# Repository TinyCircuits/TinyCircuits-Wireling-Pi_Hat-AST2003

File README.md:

# TinyCircuits Wireling Pi Hat AST2003
# AST2003 Rev2

The design files are located under design_files/ for the TinyCircuits AST2003 Rev 2 PCB. This is a Pi Hat that allows Pi users to add up to 4 Wirelings to their project. 

Format is in Cadsoft Eagle format - Eagle version 6.2 was used for the original design.

For more infomation on this, check out the product page at TinyCircuits.com

# License:

Design by TinyCircuits.
All design files are released under the Creative Commons Attribution Share-Alike 3.0 License, see the following link for details: http://creativecommons.org/licenses/by-sa/3.0

All text above must be included in any redistribution or derived design

This project uses designs and concepts developed as part of the Arduino project and the LilyPad project.  The TinyCircuits design files themselves (schematics, PCB and libraries) are not directly derived from these works' design files and have been created new, however the concepts and basic architecture behind the TinyDuino and TinyLily products are derived and we thank the hard work of the organizations below for their contributions to open-source hardware:
  
Original Arduino Uno Design by Team Arduino

LilyPad Arduino Design by Leah Buechley and Sparkfun Electronics

Please support the open-source hardware community

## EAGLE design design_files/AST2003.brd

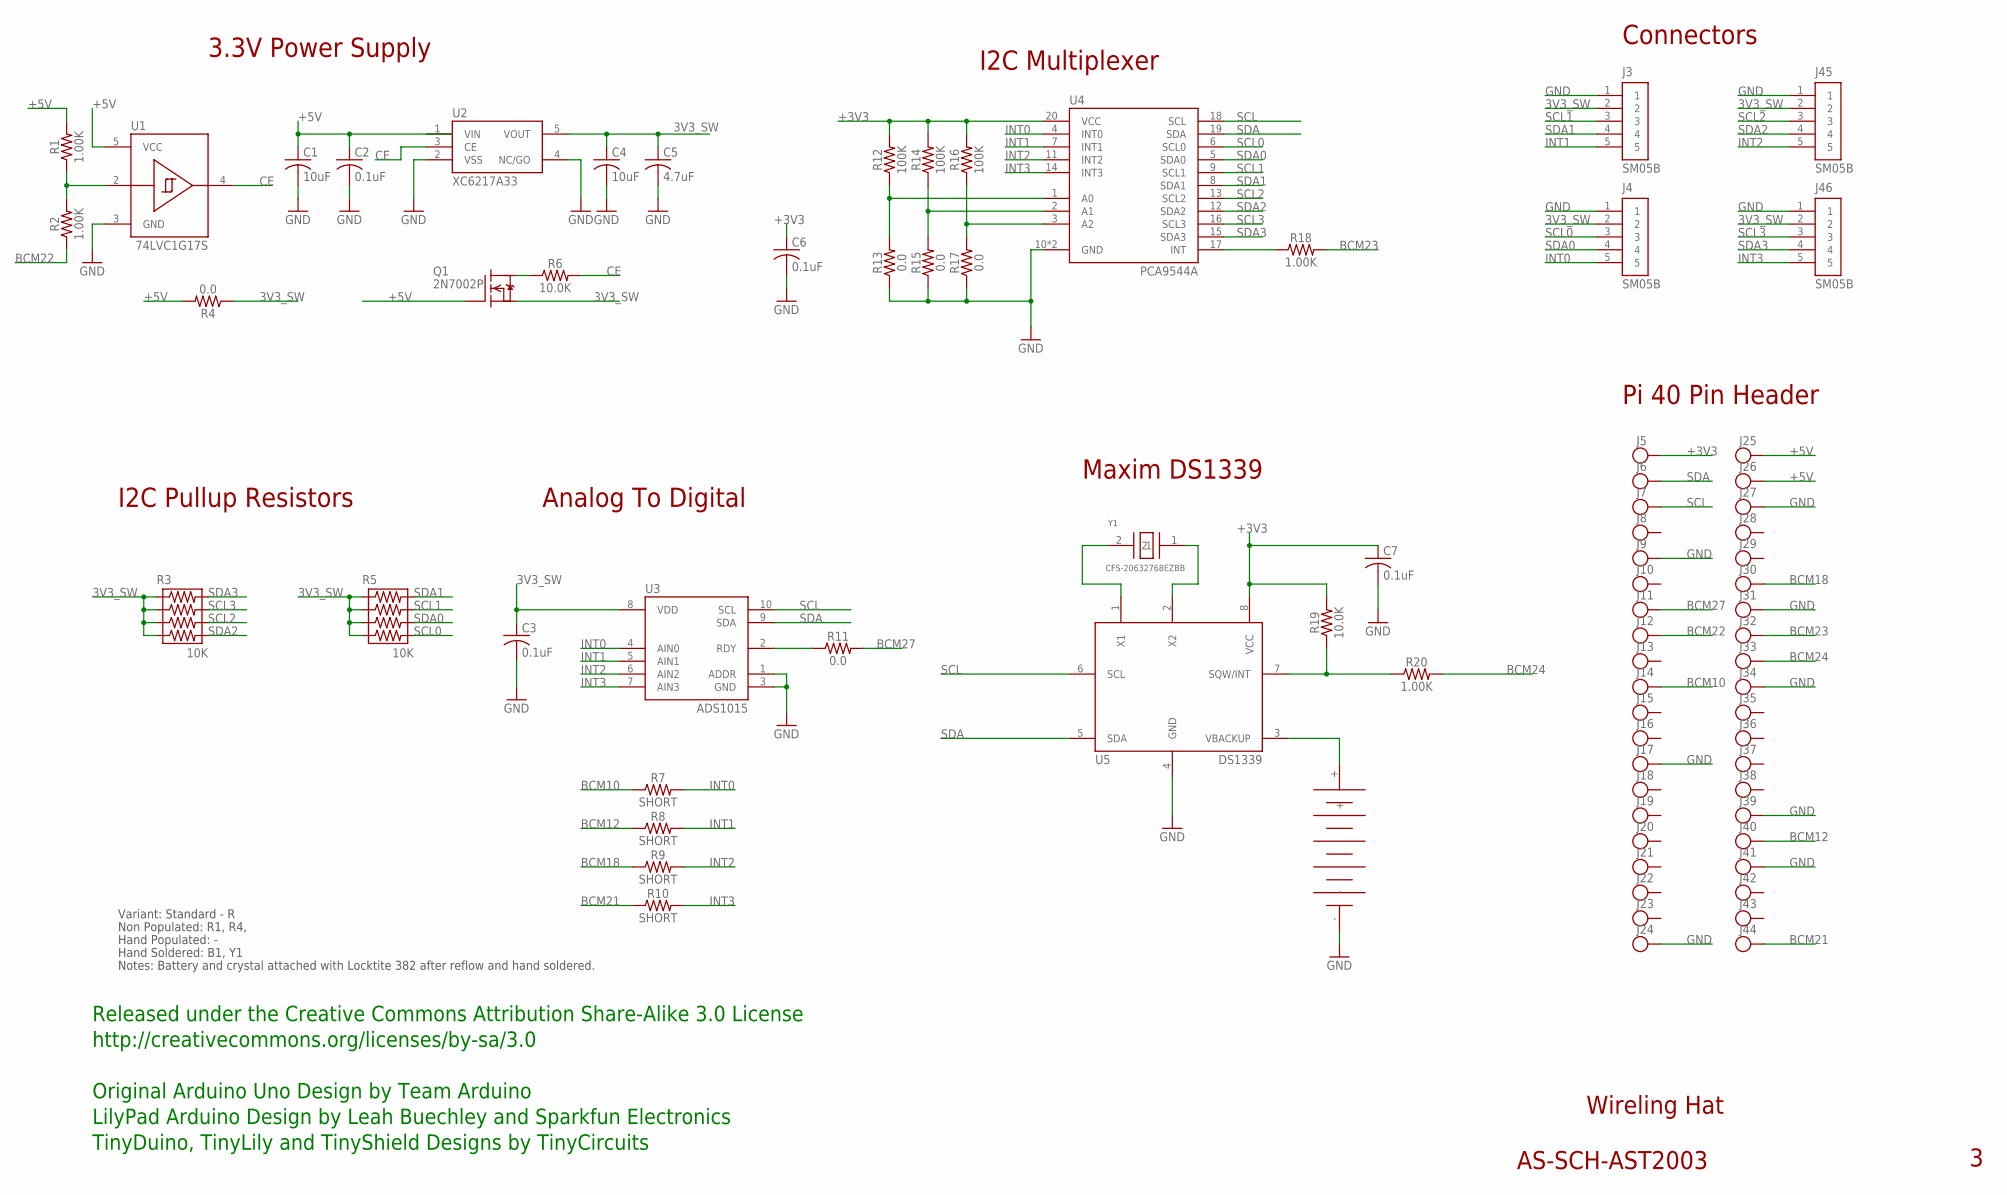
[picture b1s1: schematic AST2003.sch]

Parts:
B1: ML-920S/DN
C1, C4: 10uF; C0603; PARTNO AS-ITM-00002
C2, C6: 0.1uF; C0402; PARTNO AS-ITM-00008
C3, C7: 0.1uF; C0402
C5: 4.7uF; C0402; PARTNO AS-ITM-00242
J3, J4, J45, J46: SM05B; JST_SH_5X1
J5, J6, J7, J8, J9, J10, J11, J12, J13, J14, J15, J16, J17, J18, J19, J20, J21, J22, J23, J24, J25, J26, J27, J28, J29, J30, J31, J32, J33, J34, J35, J36, J37, J38, J39, J40, J41, J42, J43, J44: PIN_1X.1"1; 1X.1"_2
Q1: 2N7002P; SOT-416; PARTNO AS-ITM-00110
R1, R2, R20: 1.00K; 0402; PARTNO AS-ITM-00003
R3, R5: 10K; 0402RPACK; PARTNO AS-ITM-00520
R4, R13, R15, R17: 0.0; 0402; PARTNO AS-ITM-00076
R6, R19: 10.0K; 0402; PARTNO AS-ITM-00032
R7, R8, R9, R10: SHORT; 0402_SHORT
R11: 0.0; 0402
R12, R14, R16: 100K; 0402; PARTNO AS-ITM-00004
R18: 1.00K; 0402
U1: 74LVC1G17S; SOT-353
U2: XC6217A33; SOT-25; PARTNO AS-ITM-00249
U3: ADS1015; R-PQFP-N10
U4: PCA9544A; VQFN-20_4.5X3.5
U5: DS1339; 8-USOP
Y1: CFS-20632768EZBB; CRYSTAL_1.9MM_TH

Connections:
3V3_SW: C3.1, C4.1, C5.1, J3.2, J4.2, J45.2, J46.2, Q1.2 (S), R3.1, R3.3, R3.5, R3.7, R4.1, R5.1, R5.3, R5.5, R5.7, U2.5 (VOUT), U3.8 (VDD)
+3V3: C6.1, C7.1, J5.1, R12.2, R14.2, R16.2, R19.2, U4.20 (VCC), U5.8 (VCC)
+5V: C1.1, C2.1, J25.1, J26.1, Q1.1 (G), R1.2, R4.2, U1.5 (VCC), U2.1 (VIN)
BCM10: J14.1, R7.1
BCM12: J40.1, R8.1
BCM18: J30.1, R9.1
BCM21: J44.1, R10.1
BCM22: J12.1, R2.1
BCM23: J32.1, R18.2
BCM24: J33.1, R20.2
BCM27: J11.1, R11.2
CE: R6.2, U1.4 (Y), U2.3 (CE)
GND: B1.-, C1.2, C2.2, C3.2, C4.2, C5.2, C6.2, C7.2, J3.1, J4.1, J9.1, J17.1, J24.1, J27.1, J31.1, J34.1, J39.1, J41.1, J45.1, J46.1, R13.1, R15.1, R17.1, U1.3 (GND), U2.2 (VSS), U2.4 (NC/GO), U3.1 (ADDR), U3.3 (GND), U4.10 (GND), U4.PAD (GND), U5.4 (GND)
INT0: J4.5, R7.2, U3.4 (AIN0), U4.4 (INT0)
INT1: J3.5, R8.2, U3.5 (AIN1), U4.7 (INT1)
INT2: J45.5, R9.2, U3.6 (AIN2), U4.11 (INT2)
INT3: J46.5, R10.2, U3.7 (AIN3), U4.14 (INT3)
unnamed: Q1.3 (D), R6.1
unnamed: R12.1, R13.2, U4.1 (A0)
unnamed: R16.1, R17.2, U4.3 (A2)
unnamed: R18.1, U4.17 (INT)
unnamed: R14.1, R15.2, U4.2 (A1)
unnamed: R11.1, U3.2 (RDY)
unnamed: R19.1, R20.1, U5.7 (SQW/INT)
unnamed: B1.+, U5.3 (VBACKUP)
unnamed: U5.1 (X1), Y1.2 (1)
unnamed: U5.2 (X2), Y1.1 (2)
unnamed: R1.1, R2.2, U1.2 (A)
SCL: J7.1, U3.10 (SCL), U4.18 (SCL), U5.6 (SCL)
SCL0: J4.3, R5.8, U4.6 (SCL0)
SCL1: J3.3, R5.4, U4.9 (SCL1)
SCL2: J45.3, R3.6, U4.13 (SCL2)
SCL3: J46.3, R3.4, U4.16 (SCL3)
SDA: J6.1, U3.9 (SDA), U4.19 (SDA), U5.5 (SDA)
SDA0: J4.4, R5.6, U4.5 (SDA0)
SDA1: J3.4, R5.2, U4.8 (SDA1)
SDA2: J45.4, R3.8, U4.12 (SDA2)
SDA3: J46.4, R3.2, U4.15 (SDA3)

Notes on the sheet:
Wireling Hat
AS-SCH-AST2003
Released under the Creative Commons Attribution Share-Alike 3.0 License
http://creativecommons.org/licenses/by-sa/3.0
LilyPad Arduino Design by Leah Buechley and Sparkfun Electronics
TinyDuino, TinyLily and TinyShield Designs by TinyCircuits
Original Arduino Uno Design by Team Arduino
3.3V Power Supply
I2C Multiplexer
Connectors
Analog To Digital
I2C Pullup Resistors
Non Populated: R1, R4,
Hand Populated: -
Hand Soldered: B1, Y1
Notes: Battery and crystal attached with Locktite 382 after reflow and hand soldered.
Variant: Standard - R
Maxim DS1339
Pi 40 Pin Header

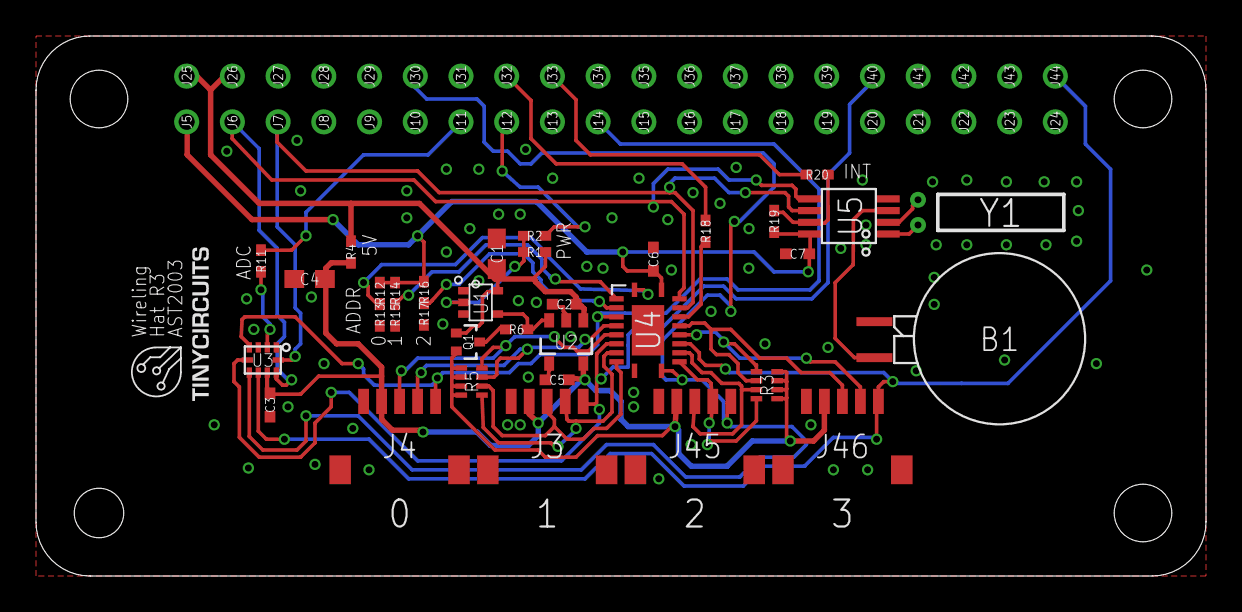
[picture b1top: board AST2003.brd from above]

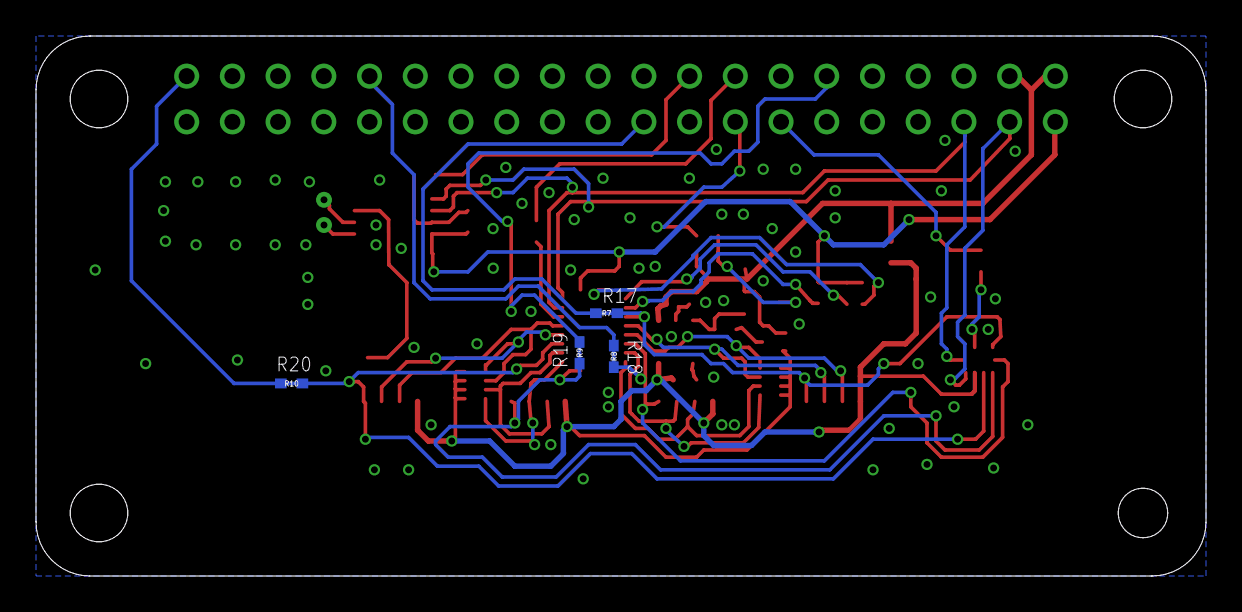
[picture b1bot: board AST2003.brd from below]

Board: 2 copper layers, 65.0 x 30.0 mm, 80 parts (4 on the bottom side), 38 nets.

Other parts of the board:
U$1: DOCFIELD-TINYCIRCUITS-PCB

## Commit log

2019-12-17 updated documentation
